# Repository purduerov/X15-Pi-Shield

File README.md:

# Readme for X15-Pi-Shield

Whenever you make a new part, download the datasheet and save it here _**and**_ with the part in the parts library

Always pull other people's changes before beginning to work
`git pull`

Be sure to push your changes after  working on them. Run:
1. `git add .` to add any files in this directory or a subdirectory
or `git add -u` to add any modified files
2. (Optional) `git clean -nX` to see what ignored files can be removed
	`git clean -fX` removes ignored files (Eagle backups)
3. `git commit -m "helpful commit message"` with a description of the work that you did
4. `git push` to push your work to github

Other helpful commands
* `git status` says information about modified and staged files
* `git log` shows the recent commits of the repository
* `git log filename.extension` show the recent commits for just that file
* `git checkout first-couple-letter-of-commit-id` lets you go back to a previous version
* `git checkout master` brings you back to the latest commit
* `git tag` lists the tags
* `git tag -a orderX -m "the version of the board placed for the X'th order"` tag a specific commit
* `git push --tags` needed to push tags to remote
* `git show orderX` show the commit log for the given tag
* `git checkout orderX` go back and interact with the files at the tagged commit

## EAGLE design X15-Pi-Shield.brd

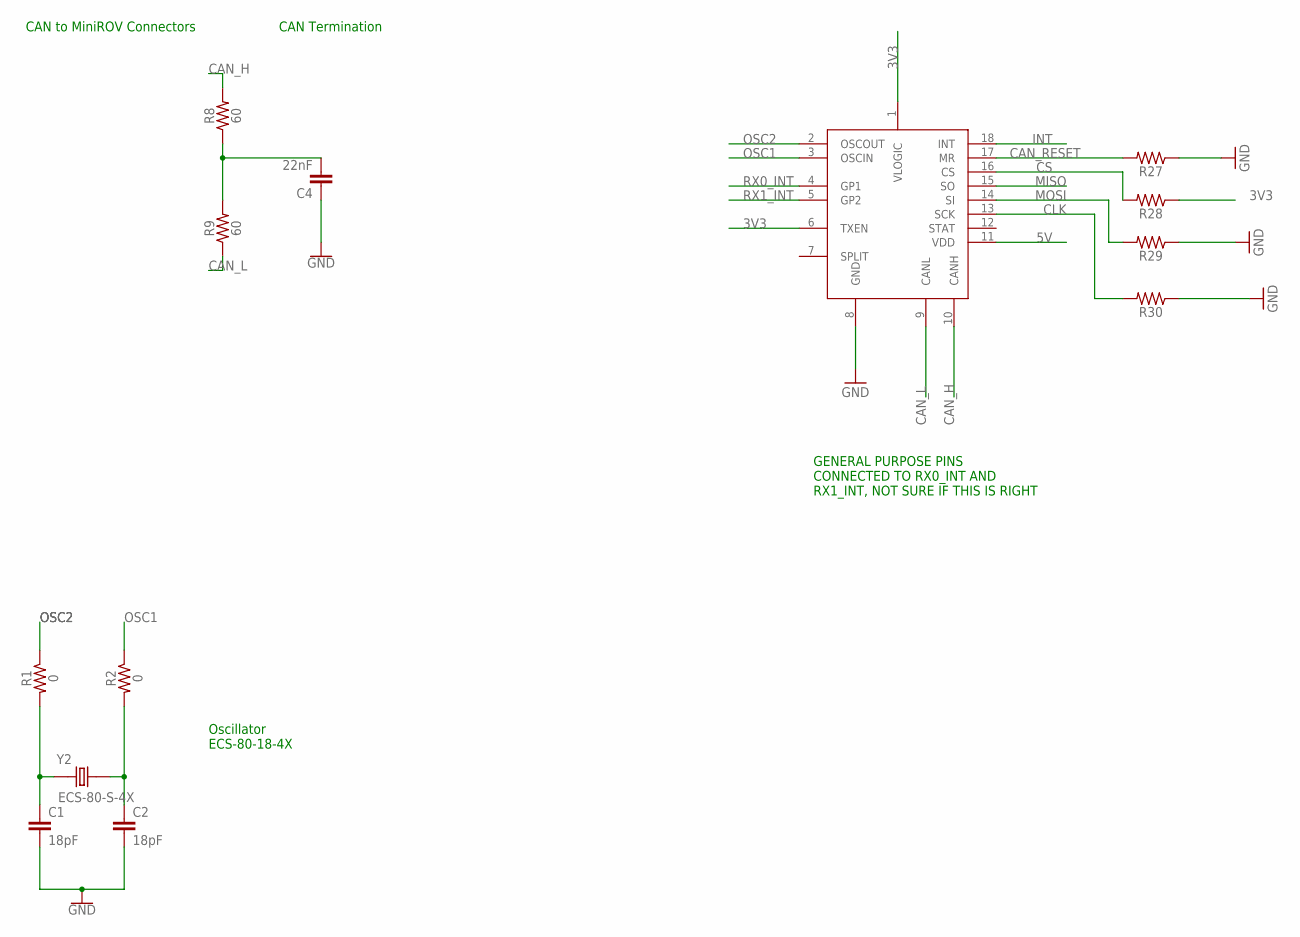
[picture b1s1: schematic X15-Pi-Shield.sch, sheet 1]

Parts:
C1, C2: 18pF; 0603
C4: 22nF; 0603
R1, R2: 0; 0603
R8, R9: 60; 0603
R27, R28, R29, R30: 50k; 0603
U$6: HI-3110; SOIC-18
Y2: ECS-80-S-4X; XTAL_ECS-80-S-4X

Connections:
3V3: R28.1, U$6.1 (VLOGIC), U$6.6 (TXEN); also elsewhere on the board
5V: U$6.11 (VDD); also elsewhere on the board
CAN_H: R8.2, U$6.10 (CANH); also elsewhere on the board
CAN_L: R9.1, U$6.9 (CANL); also elsewhere on the board
CAN_RESET: R27.2, U$6.17 (MR); also elsewhere on the board
CLK: R30.2, U$6.13 (SCK); also elsewhere on the board
CS: R28.2, U$6.16 (CS); also elsewhere on the board
GND: C1.2, C2.2, C4.1, R27.1, R29.1, R30.1, U$6.8 (GND); also elsewhere on the board
INT: U$6.18 (INT); also elsewhere on the board
MISO: U$6.15 (SO); also elsewhere on the board
MOSI: R29.2, U$6.14 (SI); also elsewhere on the board
unnamed: C1.1, R1.2, Y2.1
unnamed: C2.1, R2.2, Y2.2
unnamed: C4.2, R8.1, R9.2
OSC1: R2.1, U$6.3 (OSCIN)
OSC2: R1.1, U$6.2 (OSCOUT)
RX0_INT: U$6.4 (GP1); also elsewhere on the board
RX1_INT: U$6.5 (GP2); also elsewhere on the board

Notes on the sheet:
Oscillator ECS-80-18-4X
CAN Termination
CAN to MiniROV Connectors
GENERAL PURPOSE PINS CONNECTED TO RX0_INT AND RX1_INT, NOT SURE IF THIS IS RIGHT

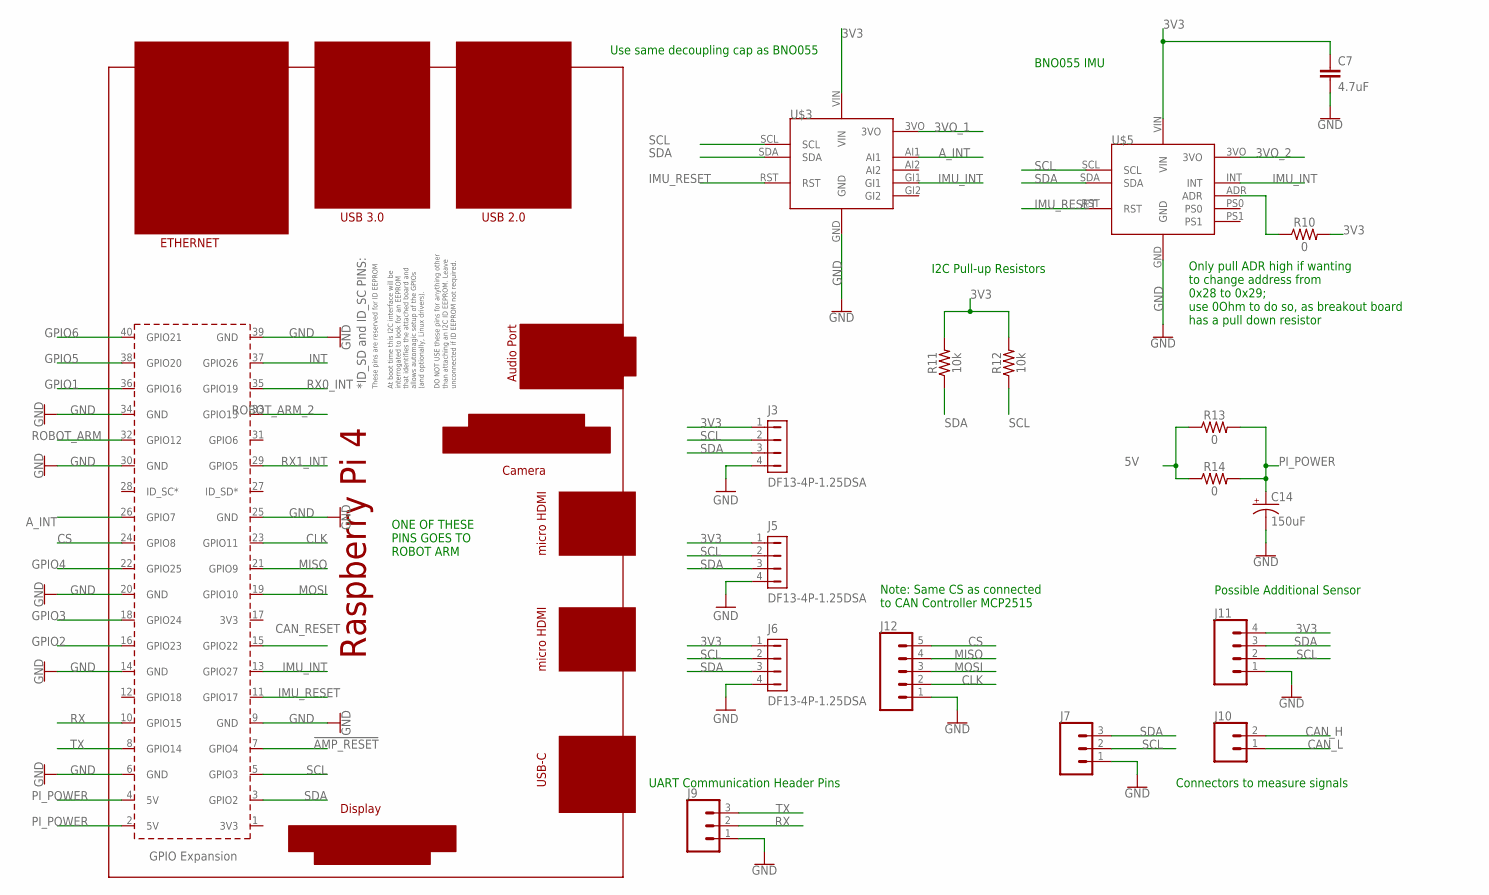
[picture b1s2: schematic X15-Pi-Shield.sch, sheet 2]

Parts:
C7: 4.7uF; 0603
C14: 150uF; 2917(7343-31-METRIC)
J3, J5, J6: DF13-4P-1.25DSA
J7, J9: CONN_03; 1X03
J10: CONN_02; 1X02
J11: CONN_04; 1X04
J12: CONN_05; 1X05
R10, R13, R14: 0; 0603
R11, R12: 10k; 0603
U$3: ADAFRUIT-FXOS8700-FXAS21002
U$4: RPI4
U$5: ADAFRUIT-BNO055

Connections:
3V3: C7.1, J3.1, J5.1, J6.1, J11.4, R10.2, R11.2, R12.2, U$3.VIN, U$5.VIN; also elsewhere on the board
3VO_1: U$3.3VO
3VO_2: U$5.3VO
5V: R13.1, R14.1; also elsewhere on the board
!AMP_RESET: U$4.7 (GPIO4); also elsewhere on the board
A_INT: U$3.AI1, U$4.26 (GPIO7)
CAN_H: J10.2; also elsewhere on the board
CAN_L: J10.1; also elsewhere on the board
CAN_RESET: U$4.15 (GPIO22); also elsewhere on the board
CLK: J12.2, U$4.23 (GPIO11); also elsewhere on the board
CS: J12.5, U$4.24 (GPIO8); also elsewhere on the board
GND: C7.2, C14.-, J3.4, J5.4, J6.4, J7.1, J9.1, J11.1, J12.1, U$3.GND, U$4.6 (GND), U$4.9 (GND), U$4.14 (GND), U$4.20 (GND), U$4.25 (GND), U$4.30 (GND), U$4.34 (GND), U$4.39 (GND), U$5.GND; also elsewhere on the board
GPIO1: U$4.36 (GPIO16); also elsewhere on the board
GPIO2: U$4.16 (GPIO23); also elsewhere on the board
GPIO3: U$4.18 (GPIO24); also elsewhere on the board
GPIO4: U$4.22 (GPIO25); also elsewhere on the board
GPIO5: U$4.38 (GPIO20); also elsewhere on the board
GPIO6: U$4.40 (GPIO21); also elsewhere on the board
IMU_INT: U$3.GI1, U$4.13 (GPIO27), U$5.INT
IMU_RESET: U$3.RST, U$4.11 (GPIO17), U$5.RST
INT: U$4.37 (GPIO26); also elsewhere on the board
MISO: J12.4, U$4.21 (GPIO9); also elsewhere on the board
MOSI: J12.3, U$4.19 (GPIO10); also elsewhere on the board
unnamed: R10.1, U$5.ADR
PI_POWER: C14.+, R13.2, R14.2, U$4.2 (5V), U$4.4 (5V)
ROBOT_ARM: U$4.32 (GPIO12); also elsewhere on the board
ROBOT_ARM_2: U$4.33 (GPIO13); also elsewhere on the board
RX: J9.2, U$4.10 (GPIO15)
RX0_INT: U$4.35 (GPIO19); also elsewhere on the board
RX1_INT: U$4.29 (GPIO5); also elsewhere on the board
SCL: J3.2, J5.2, J6.2, J7.2, J11.2, R12.1, U$3.SCL, U$4.5 (GPIO3), U$5.SCL; also elsewhere on the board
SDA: J3.3, J5.3, J6.3, J7.3, J11.3, R11.1, U$3.SDA, U$4.3 (GPIO2), U$5.SDA; also elsewhere on the board
TX: J9.3, U$4.8 (GPIO14)

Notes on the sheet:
UART Communication Header Pins
Note: Same CS as connected to CAN Controller MCP2515
Possible Additional Sensor
Connectors to measure signals
Use same decoupling cap as BNO055
I2C Pull-up Resistors
BNO055 IMU
Only pull ADR high if wanting to change address from 0x28 to 0x29; use 0Ohm to do so, as breakout board has a pull down resistor
ONE OF THESE PINS GOES TO ROBOT ARM

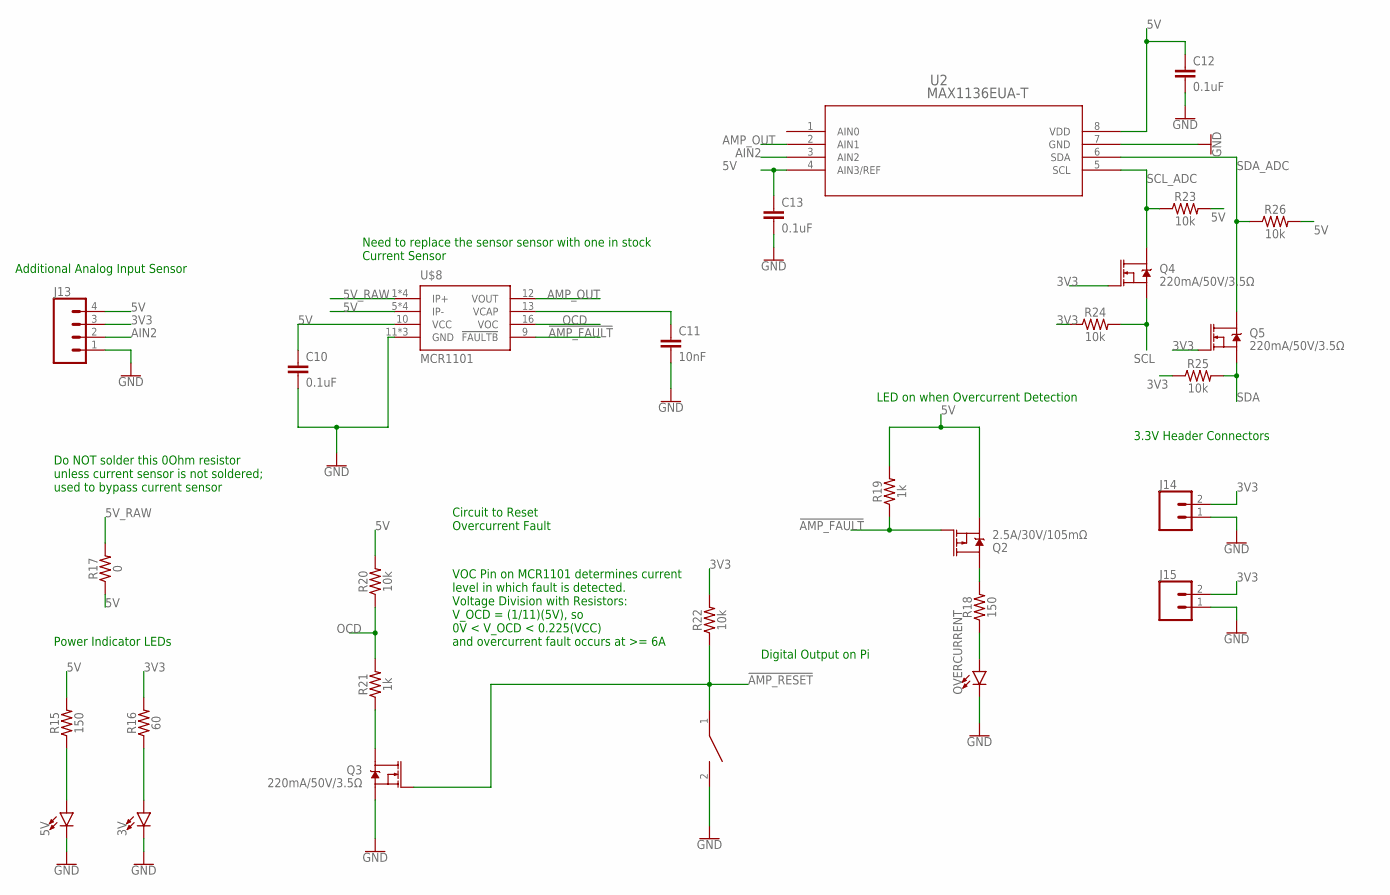
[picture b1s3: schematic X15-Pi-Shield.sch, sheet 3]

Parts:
3V, 5V: LED0603; LED-0603
C10, C12, C13: 0.1uF; 0603
C11: 10nF; 0603
J13: CONN_04; 1X04
J14, J15: CONN_02; 1X02
OVERCURRENT: LED0603; LED-0603
Q2: 2.5A/30V/105mΩ; SOT23-3
Q3, Q4, Q5: 220mA/50V/3.5Ω; SOT23-3
R15, R18: 150; 0603
R16: 60; 0603
R17: 0; 0603
R19, R21: 1k; 0603
R20, R22, R23, R24, R25, R26: 10k; 0603
U2: MAX1136EUA-T; 21-0036K
U$7: DISCRETECOMPONENTS_SWITCH; DISCRETECOMPONENTS_SW_2512
U$8: MCR1101; SOIC-16

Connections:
3V3: J13.3, J14.2, J15.2, Q4.1 (G), Q5.1 (G), R16.2, R22.2, R24.1, R25.1; also elsewhere on the board
5V: C10.1, C12.1, C13.1, J13.4, Q2.2 (S), R15.2, R17.1, R19.2, R20.2, R23.2, R26.2, U2.4 (AIN3/REF), U2.8 (VDD), U$8.5 (IP-), U$8.6 (IP-), U$8.7 (IP-), U$8.8 (IP-), U$8.10 (VCC); also elsewhere on the board
5V_RAW: R17.2, U$8.1 (IP+), U$8.2 (IP+), U$8.3 (IP+), U$8.4 (IP+)
!AMP_FAULT: Q2.1 (G), R19.1, U$8.9 (!FAULTB)
!AMP_RESET: Q3.1 (G), R22.1, U$7.1; also elsewhere on the board
AIN2: J13.2, U2.3 (AIN2)
AMP_OUT: U2.2 (AIN1), U$8.12 (VOUT)
GND: 3V.C, 5V.C, C10.2, C11.2, C12.2, C13.2, J13.1, J14.1, J15.1, OVERCURRENT.C, Q3.2 (S), U2.7 (GND), U$7.2, U$8.11 (GND), U$8.14 (GND), U$8.15 (GND); also elsewhere on the board
unnamed: 5V.A, R15.1
unnamed: 3V.A, R16.1
unnamed: C11.1, U$8.13 (VCAP)
unnamed: Q2.3 (D), R18.2
unnamed: OVERCURRENT.A, R18.1
unnamed: Q3.3 (D), R21.1
OCD: R20.1, R21.2, U$8.16 (VOC)
SCL: Q4.2 (S), R24.2; also elsewhere on the board
SCL_ADC: Q4.3 (D), R23.1, U2.5 (SCL)
SDA: Q5.2 (S), R25.2; also elsewhere on the board
SDA_ADC: Q5.3 (D), R26.1, U2.6 (SDA)

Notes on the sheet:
Do NOT solder this 0Ohm resistor unless current sensor is not soldered; used to bypass current sensor
Power Indicator LEDs
Additional Analog Input Sensor
3.3V Header Connectors
LED on when Overcurrent Detection
Circuit to Reset Overcurrent Fault
VOC Pin on MCR1101 determines current level in which fault is detected. Voltage Division with Resistors: V_OCD = (1/11)(5V), so 0V < V_OCD < 0.225(VCC) and overcurrent fault occurs at >= 6A
Digital Output on Pi
Need to replace the sensor sensor with one in stock Current Sensor

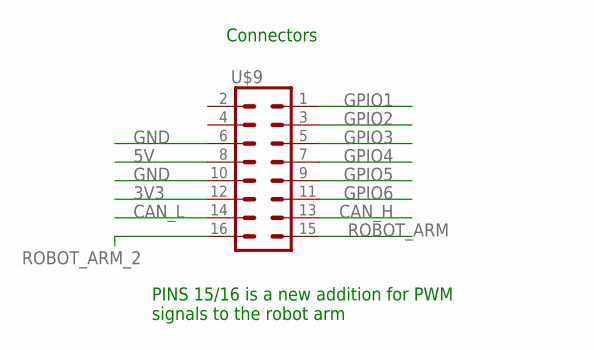
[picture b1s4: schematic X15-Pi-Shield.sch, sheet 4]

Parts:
U$9: 8X_CONN; IPL7X2

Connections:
3V3: U$9.12 (23); also elsewhere on the board
5V: U$9.8 (19); also elsewhere on the board
CAN_H: U$9.13 (1); also elsewhere on the board
CAN_L: U$9.14 (2); also elsewhere on the board
GND: U$9.6 (17), U$9.10 (21); also elsewhere on the board
GPIO1: U$9.1 (14); also elsewhere on the board
GPIO2: U$9.3 (16); also elsewhere on the board
GPIO3: U$9.5 (18); also elsewhere on the board
GPIO4: U$9.7 (20); also elsewhere on the board
GPIO5: U$9.9 (22); also elsewhere on the board
GPIO6: U$9.11 (24); also elsewhere on the board
ROBOT_ARM: U$9.15 (4); also elsewhere on the board
ROBOT_ARM_2: U$9.16 (3); also elsewhere on the board

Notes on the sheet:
Connectors
PINS 15/16 is a new addition for PWM signals to the robot arm

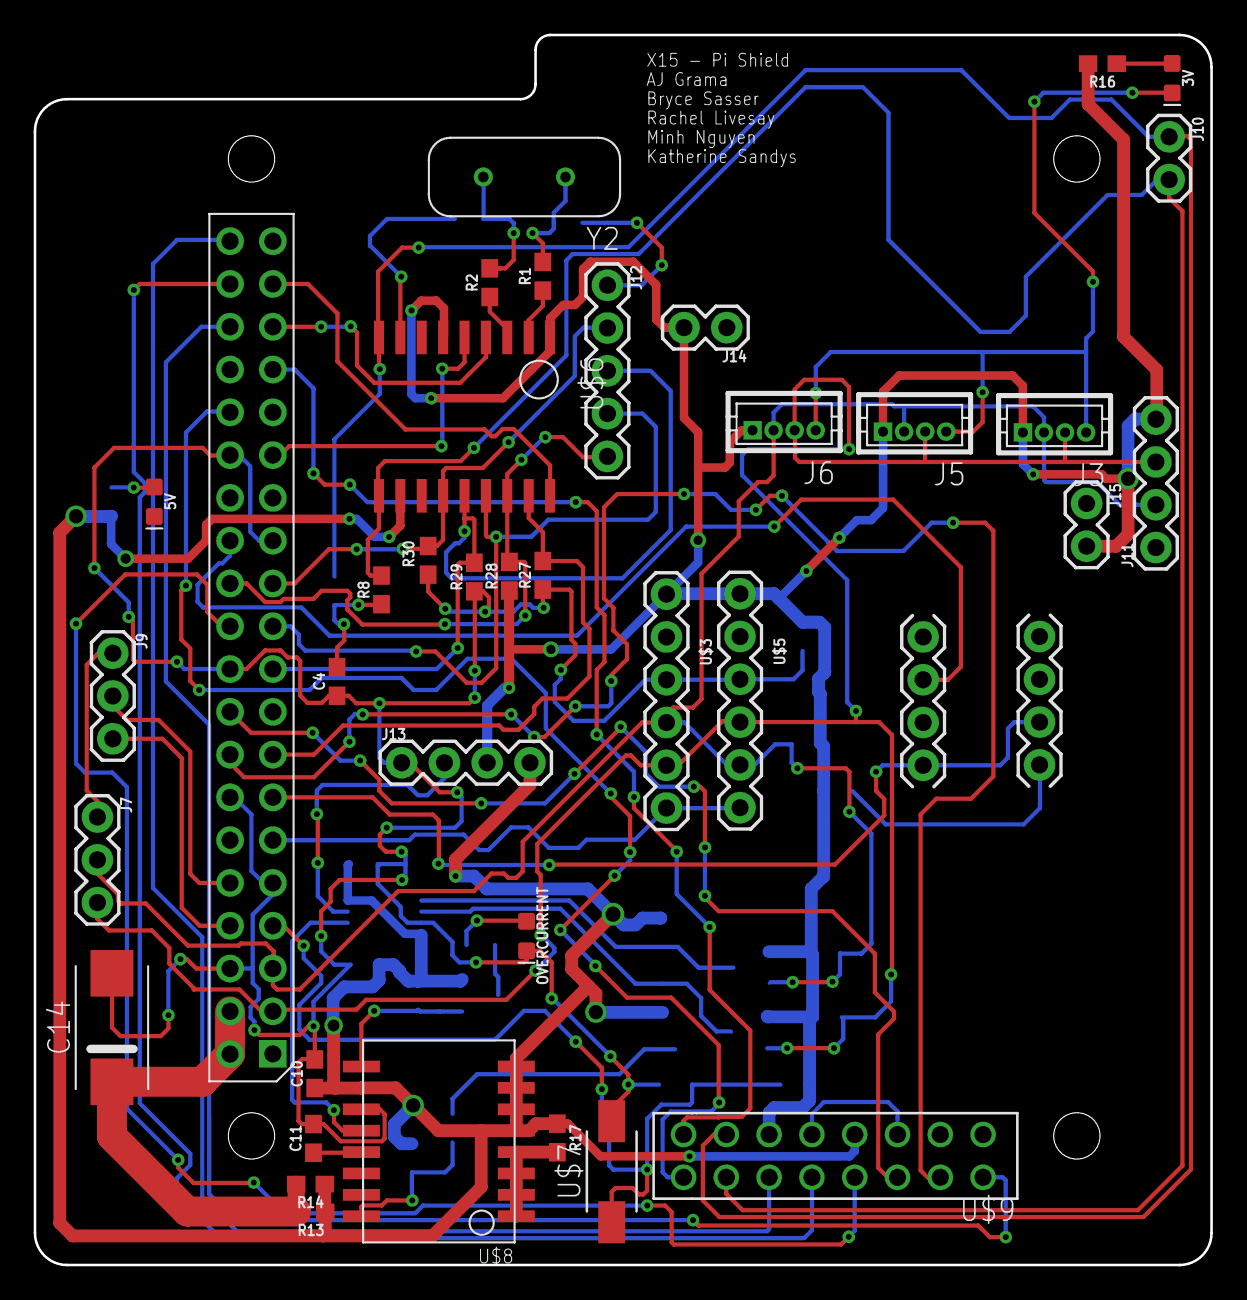
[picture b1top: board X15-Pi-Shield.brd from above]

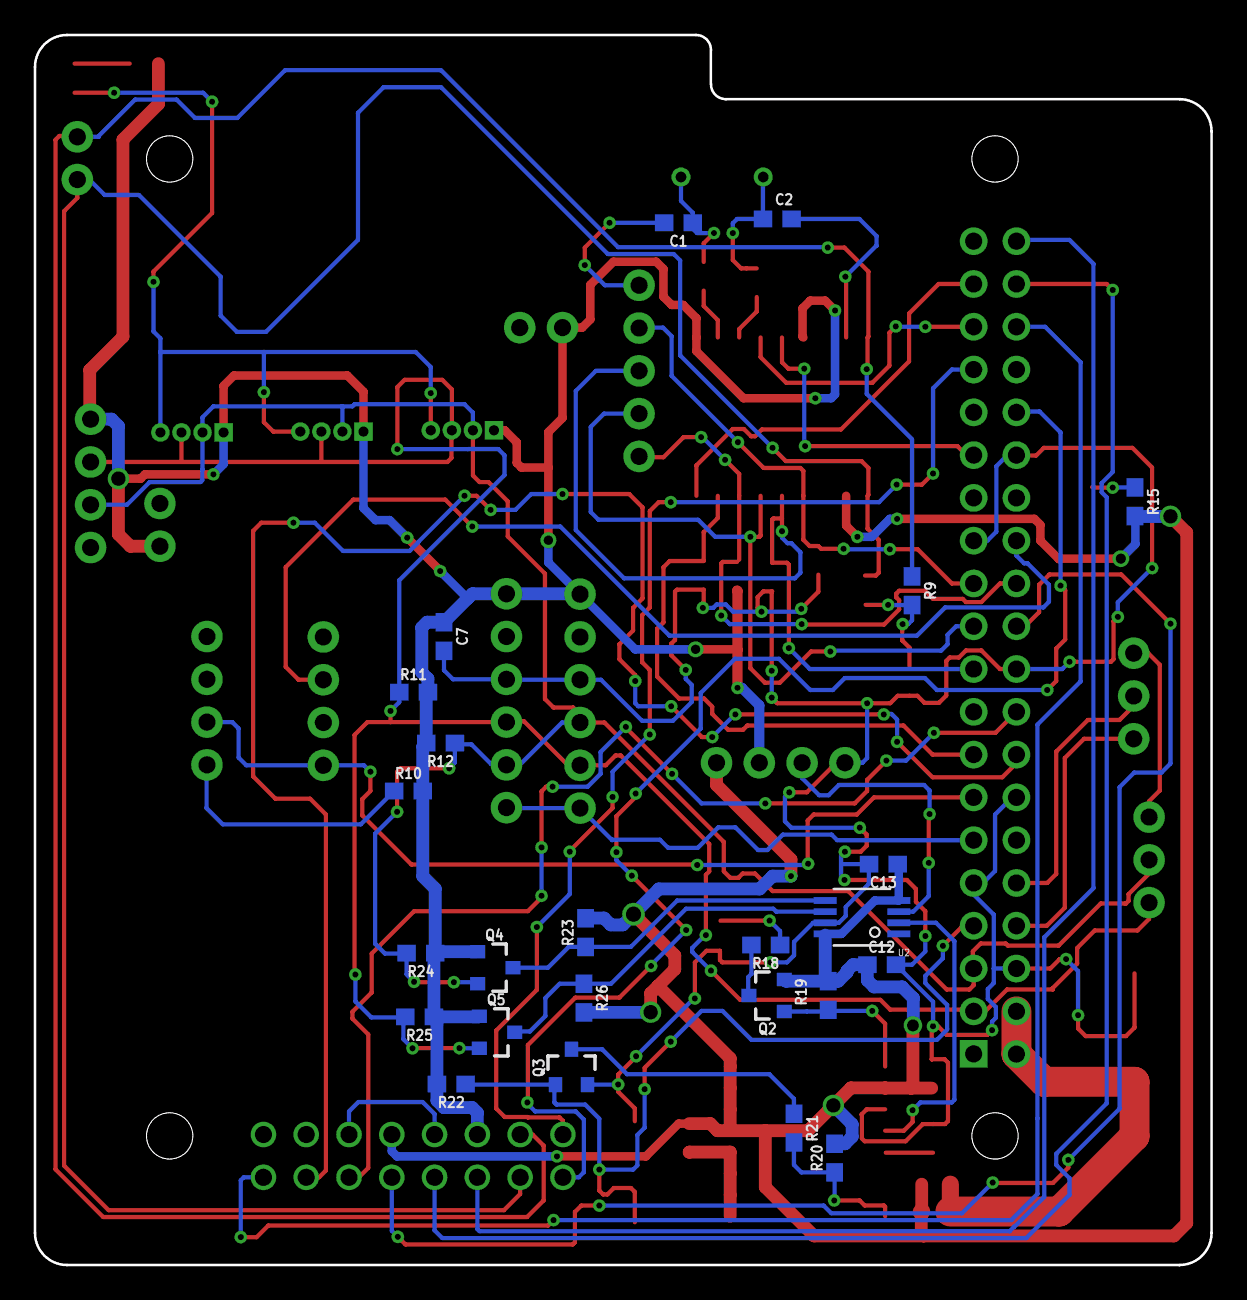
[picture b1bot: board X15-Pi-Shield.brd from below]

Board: 2 copper layers, 69.8 x 73.0 mm, 61 parts (24 on the bottom side), 49 nets.

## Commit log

2022-09-21 Starting Board
2022-09-21 Empty starting board + schematic
2022-10-15 First Schematic Draft
2022-10-15 First Schematic
2022-10-15 fixed ground and parts library
2022-10-15 2nd try
2022-10-15 Board Dimensions
2022-10-22 help me mr. bryce sir
2022-10-22 please help bryce
2022-10-22 hi bryce
2022-10-26 Board Dimensions AGAIN
2022-10-27 AAAAAAAAAAA
2022-11-05 I'm slowly losing my mind
2022-12-01 Hi Katherine
2022-12-03 r/RoastMe
2022-12-03 I swear its good this time
2022-12-03 AAAAAAAAAAAAAAAAAAAAAAAAAAA
2022-12-08 AAAA
2022-12-08 ASAIDFNODIWBEOIYBF
2022-12-08 HI :D
2022-12-10 Names n Picture

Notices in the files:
parts and their libraries:
SparkFun-Capacitors: Licensing: Creative Commons ShareAlike 4.0 International - https://creativecommons.org/licenses/by-sa/4.0
